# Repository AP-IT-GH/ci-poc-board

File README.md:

# Connected Island Proof of Concept Board

This board is used to gather data from many different sensors and send it over a LoRa network. 
The MCU on the board is an AT SAM D21 chosen because of it's low power capabilities and the extensive I/O options.
On board we have:
- 3 USART connection headers
- 1 I²C connection header
- 1 programming & debug connection
- RN2483 LoRaWAN module

The board can be powered with a voltage between 6.3V and 15V.

This document can be used to understand our reasoning behind certain choices and to learn how the board works. On the bottom we have a few improvements and suggestions for future versions.

The Bill of Materials to assemble the PCB can be found [here](./assets/bom/ibom.html) in HTML format.

## First Version

<figure>
<iframe src="https://myap84.autodesk360.com/shares/public/SH35dfcQT936092f0e434feaf45240fcc95f?mode=embed" width="1024" height="768" allowfullscreen="true" webkitallowfullscreen="true" mozallowfullscreen="true"  frameborder="0"></iframe>
<figcaption >Interactive 3D model of the PCB</figcaption>
</figure>

<figure>

<figcaption >Figure 1: Main Schematic</figcaption>
</figure>

<figure>

<figcaption >Figure 2: Power Regulators Schematic</figcaption>
</figure>

<figure>

<figcaption >Figure 3: RN2483 LoRaWAN module Schematic</figcaption>
</figure>

### Power Delivery

We are using a Li-Po 2 Cell battery and a LD1117 as 3.3V and 5V regulator

Li-Po 2 Cell: [Store](https://www.conrad.be/p/conrad-energy-lipo-accupack-74-v-2400-mah-aantal-cellen-2-20-c-softcase-xt60-1344133), [Datasheet](https://asset.conrad.com/media10/add/160267/c1/-/en/001344133SD01/veiligheidsvoorschriften-1344133-conrad-energy-lipo-accupack-74-v-2400-mah-aantal-cellen-2-20-c-softcase-xt60.pdf)

LD1117: [Store](https://www.conrad.be/p/stmicroelectronics-ld1117av33-spanningsregelaar-lineair-to-220ab-positief-vast-1-a-1184973), [Datasheet](https://asset.conrad.com/media10/add/160267/c1/-/en/001184973DS01/datablad-1184973-stmicroelectronics-ld1117av33-spanningsregelaar-lineair-to-220ab-positief-vast-1-a.pdf)

The LD1117 IC's are connected according to "Figure 3. Application circuit (for fixed output voltages)". 1x 5V en 1x 3.3V.

The dropout voltage of these regulators is 1.05V if we're counting for a 500mAh load. to get an output voltage of 5V, the regulator needs an input voltage of 5V + 1.05V = 6.05V. Thus our battery voltage has to stay above that value.

ADC voltage divider for battery:

R1 = 10 kOhm; R2 = 4.7 kOhm

### AT SAMD 21 Schematic Checklist

Datasheet p1108-p1118

#### Power Supply Connections

- [x] Check L1 10µH footprint. (https://be.farnell.com/tdk/vls201612hbx-100m-1/inductor-10uh-20-0-79a-shld/dp/2455369 ) (https://www.farnell.com/datasheets/2608157.pdf )

The MCU has two DVVIO pins (pin17 en pin36), these are internally connected to each other so only pin17 is in use.

#### External Analog Reference Connections

Not necessary because we are not using any external analog references.

#### External Reset Circuit

EFT = electrical fast transients -> spark when pressing a button

We don't need this EFT Immunity Enhancement so we're using "Figure 45-4. External Reset Circuit Schematic".

#### Clocks and Crystal Oscillators

[Understanding the SAM D21 clocks](https://blog.thea.codes/understanding-the-sam-d21-clocks/)

We keep the option to use an external 32,768kHz clock free, when not in use it doesn't have to be soldered on the PCB.

- [Capacitor](https://be.farnell.com/multicomp/mc0805n180j500ct/cap-18pf-50v-5-c0g-np0-0805/dp/1759194): MC0805N180J500CT, 18 pF, 0805
- [Crystal](https://be.farnell.com/fox-electronics/fx135a-327/crystal-32-768khz-12-5pf-smd/dp/2064037): FX135A-327, 32.768 kHz, SMD

Connected according to: "Figure 45-9. External Real Time Oscillator with Load Capacitor".

`XIN32` and `XOUT32` are on the only available connections for SERCOM1 (PA00 en PA01) so SERCOM1 will not be used.

#### Programming and Debug Ports

Pull-up resistor on SWCLK!

We are using "Figure 45-12. 10-pin JTAGICE3 Compatible Serial Wire Debug Interface".

#### USB Interface

We are not using the USB interface.

### SERCOM Aansluiten

The used SERCOM pins of the SAM D21 got a `SERCOMx_PADn_y` label for easy reference on the scheme and PCB. The Atmel START configuration was used as a reference.

SERCOM-ALT [ref1](https://microchipsupport.force.com/s/article/SERCOM-muxing-on-SAM-D-L-C-devices), [ref2](https://learn.adafruit.com/using-atsamd21-sercom-to-add-more-spi-i2c-serial-ports/muxing-it-up)

| Use case | SERCOM  | Pins           | Function                                                     |
| ------- | ------- | ---------------- | ----------------------------------------------------------- |
| RN2384  | SERCOM0 | PA04, PA05, PA07 | TX, RX, <span style="text-decoration:overline">RESET</span> |
| USART_1 | SERCOM5 | PA22, PA23       | TX, RX                                                      |
| USART_2 | SERCOM2 | PA08, PA09       | TX, RX                                                      |
| USART_3 | SERCOM3 | PA16, PA17       | TX, RX                                                      |
| I2C_0   | SERCOM4 | PA12, PA13       | SDA, SCL                                                    |

> If the PA24 and PA25 pins are not connected, it is recommended to enable a pull-up on PA24 and PA25 through input GPIO mode. The aim is to avoid an eventually extract power consumption (<1mA) due to a not stable level on pad. The port PA24 and PA25 doesn't have Drive Strength option. (these are the USB pins). 

[ATSAMD D21 Datasheet](https://ww1.microchip.com/downloads/en/DeviceDoc/SAM-D21DA1-Family-Data-Sheet-DS40001882G.pdf)

### RN2483 LoRaWAN module

[RN2483 Datasheet](https://ww1.microchip.com/downloads/en/DeviceDoc/RN2483-Low-Power-Long-Range-LoRa-Technology-Transceiver-Module-DS50002346F.pdf) 

Reuse of symbol from the older AirQualitySensor project.

`PA6` who is connected to `RN2384_RESET` should always be HIGH. You can reset the RN2483 module by setting the pin LOW for a moment.

<u>Are we using `UART_CTS` and `UART_RTS` as a handshake mechanism?</u>: No

<u>Do we connect the Internal Program Pins with the 6-pin ICSP header on our PCB?</u>: No

We are using RFH for 868MHz communication.

> When routing RF paths, use proper strip lines with an impedance of 50 Ohm.

We are not using the GPIO pins of the module.

## Future Versions

Luckily, the first version of this board works. Of course we have a few remarks to make for future versions of this board. 
A short summary:
- More marks on the silkscreen explaining the pinout of headers
- A different battery connector
- Adding a USB port
- Placing components on the back

### Markings

The first version of the board doesn't show any markings for the pinout of the headers. The battery connector doesn't even have a polarity marking. 

### Battery Connector

The current battery connector is very small and not very useful. A specific new connector has not been chosen yet.

### USB Port

We think that a USB port on the PCB would be very useful. There exists a bootloader for the ATSAMD 21 that enables users to program the board with CircuitPython. This might make the board easier to use. Other bootloaders enable the use of the Arduino IDE instead of Microchip Studio. 
Right now the board can only be programmed with a J-LINK or Atmel ICE programmer. 

### Components on the Back

Right now every component on the board is positioned on the front. We think a lot of space can be saved by placing some SMD components on the back.

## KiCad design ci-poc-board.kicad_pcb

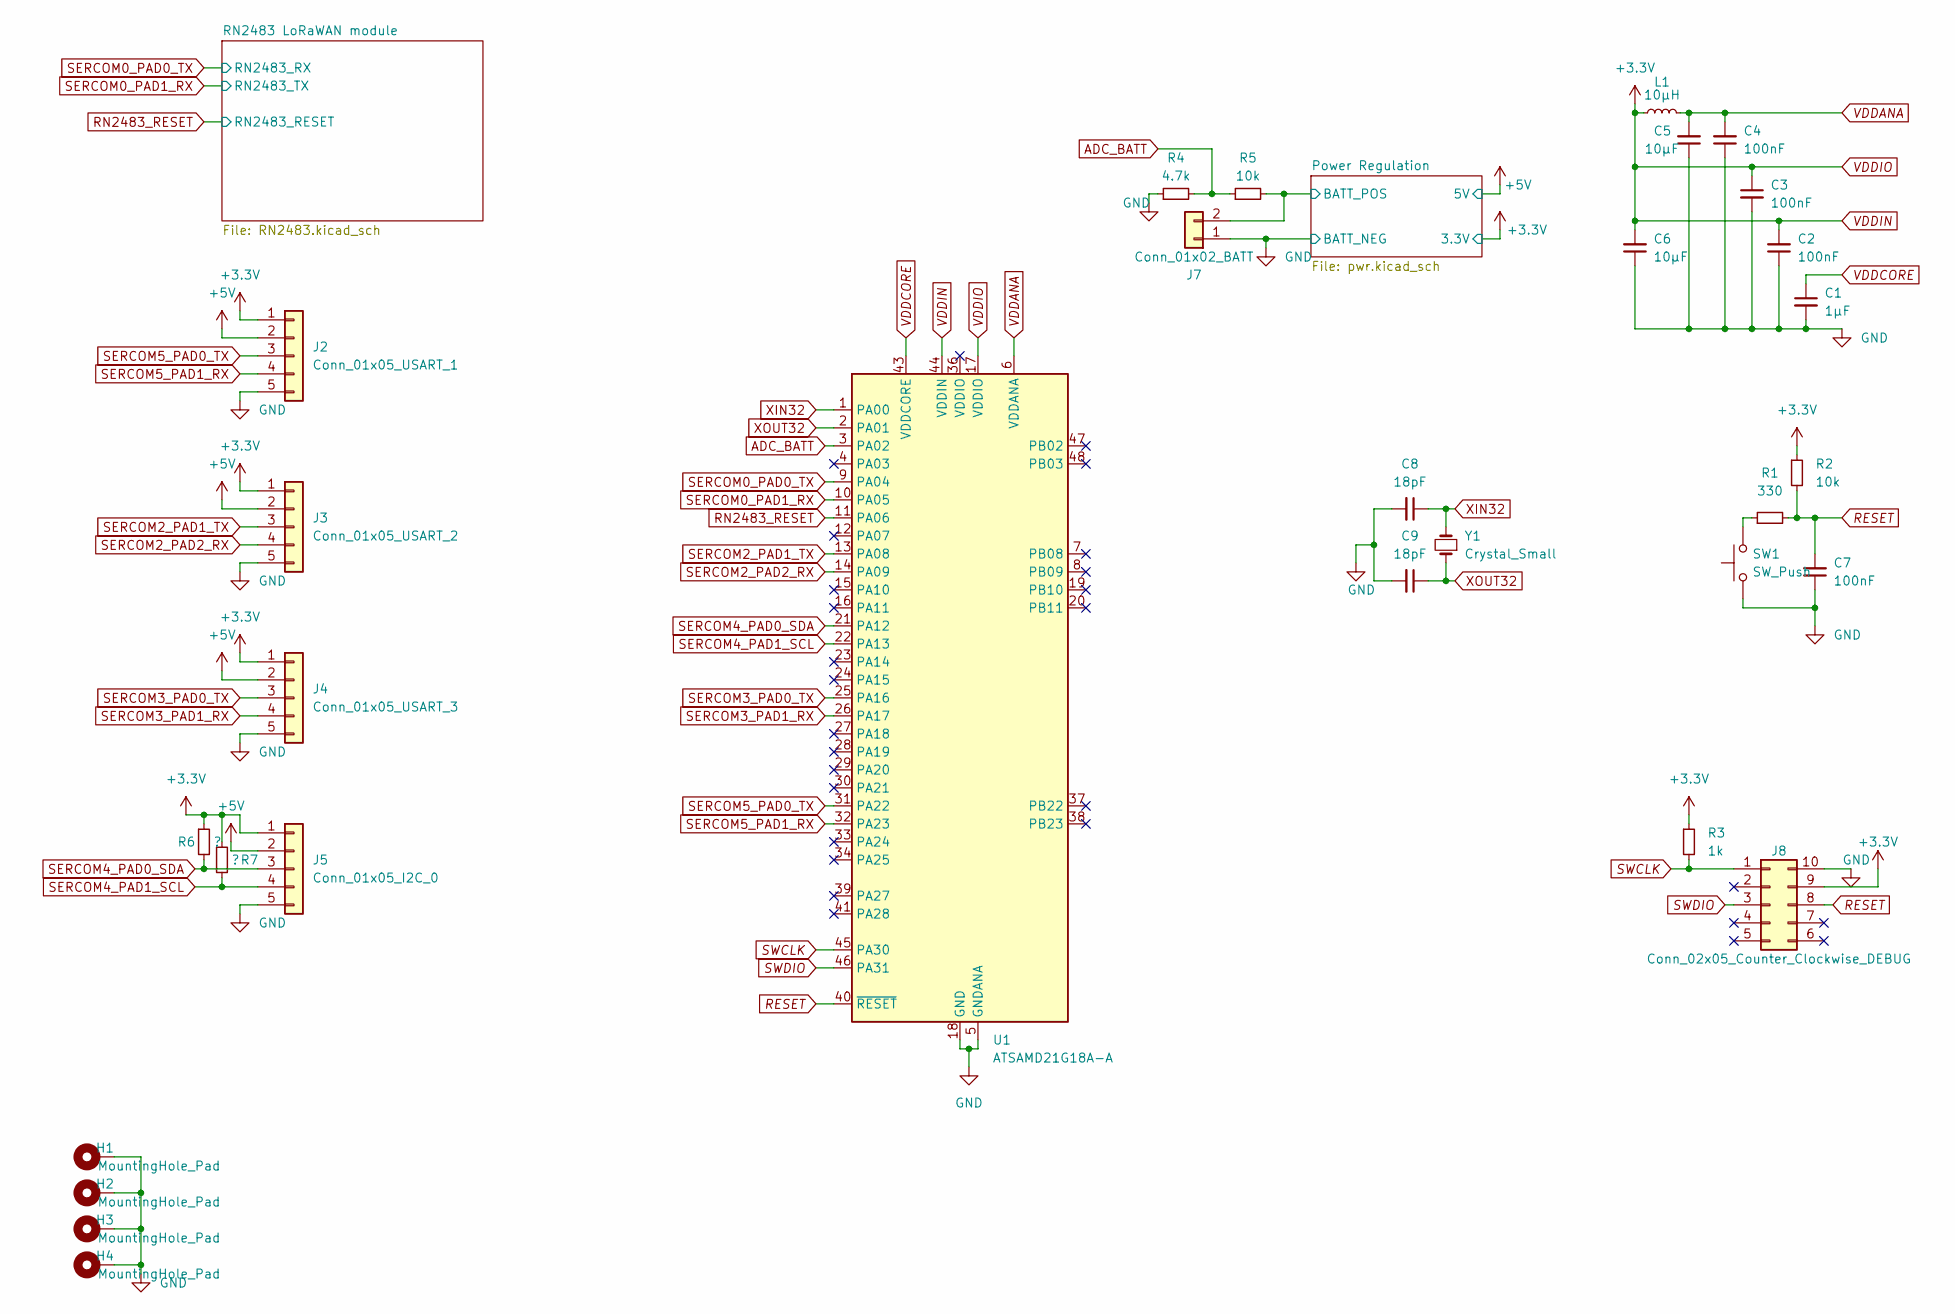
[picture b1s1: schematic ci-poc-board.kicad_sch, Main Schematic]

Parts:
C1: 1µF; C_0805_2012Metric_Pad1.18x1.45mm_HandSolder
C2, C3, C4, C7: 100nF; C_0805_2012Metric_Pad1.18x1.45mm_HandSolder
C5, C6: 10µF; C_0805_2012Metric_Pad1.18x1.45mm_HandSolder
C8, C9: 18pF; C_0805_2012Metric_Pad1.18x1.45mm_HandSolder
H1, H2, H3, H4: MountingHole_Pad; MountingHole_3.2mm_M3_DIN965_Pad
J2: Conn_01x05_USART_1; JST_XH_B5B-XH-A_1x05_P2.50mm_Vertical
J3: Conn_01x05_USART_2; JST_XH_B5B-XH-A_1x05_P2.50mm_Vertical
J4: Conn_01x05_USART_3; JST_XH_B5B-XH-A_1x05_P2.50mm_Vertical
J5: Conn_01x05_I2C_0; JST_XH_B5B-XH-A_1x05_P2.50mm_Vertical
J7: Conn_01x02_BATT; JST_PH_B2B-PH-K_1x02_P2.00mm_Vertical
J8: Conn_02x05_Counter_Clockwise_DEBUG; PinHeader_2x05_P2.54mm_Vertical
L1: 10µH; L_Murata_LQH2MCNxxxx02_2.0x1.6mm
R1: 330; R_0805_2012Metric_Pad1.20x1.40mm_HandSolder
R2, R5: 10k; R_0805_2012Metric_Pad1.20x1.40mm_HandSolder
R3: 1k; R_0805_2012Metric_Pad1.20x1.40mm_HandSolder
R4: 4.7k; R_0805_2012Metric_Pad1.20x1.40mm_HandSolder
R6, R7: ?; R_0805_2012Metric_Pad1.20x1.40mm_HandSolder
SW1: SW_Push; SW_Push_1P1T_NO_6x6mm_H9.5mm
U1: ATSAMD21G18A-A; TQFP-48_7x7mm_P0.5mm
Y1: Crystal_Small; Crystal_SMD_3215-2Pin_3.2x1.5mm

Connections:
+5V: J2.2, J3.2, J4.2, J5.2; also elsewhere on the board
/Power Regulation/BATT_POS: J7.2, R5.2; also elsewhere on the board
ADC_BATT: R4.2, R5.1, U1.3 (PA02)
GND: C1.2, C2.1, C3.2, C4.1, C5.1, C6.1, C7.1, C8.2, C9.2, H1.1, H2.1, H3.1, H4.1, J2.5, J3.5, J4.5, J5.5, J7.1, J8.10, R4.1, SW1.2, U1.5 (GNDANA), U1.18 (GND), U1.35 (GND), U1.42 (GND); also elsewhere on the board
unnamed: R1.1, SW1.1
RESET: C7.2, J8.8, R1.2, R2.2, U1.40 (~RESET)
RN2483_RESET: U1.11 (PA06); also elsewhere on the board
SERCOM0_PAD0_TX: U1.9 (PA04); also elsewhere on the board
SERCOM0_PAD1_RX: U1.10 (PA05); also elsewhere on the board
SERCOM2_PAD1_TX: J3.3, U1.13 (PA08)
SERCOM2_PAD2_RX: J3.4, U1.14 (PA09)
SERCOM3_PAD0_TX: J4.3, U1.25 (PA16)
SERCOM3_PAD1_RX: J4.4, U1.26 (PA17)
SERCOM4_PAD0_SDA: J5.3, R6.2, U1.21 (PA12)
SERCOM4_PAD1_SCL: J5.4, R7.2, U1.22 (PA13)
SERCOM5_PAD0_TX: J2.3, U1.31 (PA22)
SERCOM5_PAD1_RX: J2.4, U1.32 (PA23)
SWCLK: J8.1, R3.2, U1.45 (PA30)
SWDIO: J8.3, U1.46 (PA31)
VDDANA: C4.2, C5.2, L1.2, U1.6 (VDDANA)
VDDCORE: C1.1, U1.43 (VDDCORE)
VDDIN: C2.2, C3.1, C6.2, J2.1, J3.1, J4.1, J5.1, J8.9, L1.1, R2.1, R3.1, R6.1, R7.1, U1.17 (VDDIO), U1.44 (VDDIN); also elsewhere on the board
XIN32: C8.1, U1.1 (PA00), Y1.2
XOUT32: C9.1, U1.2 (PA01), Y1.1

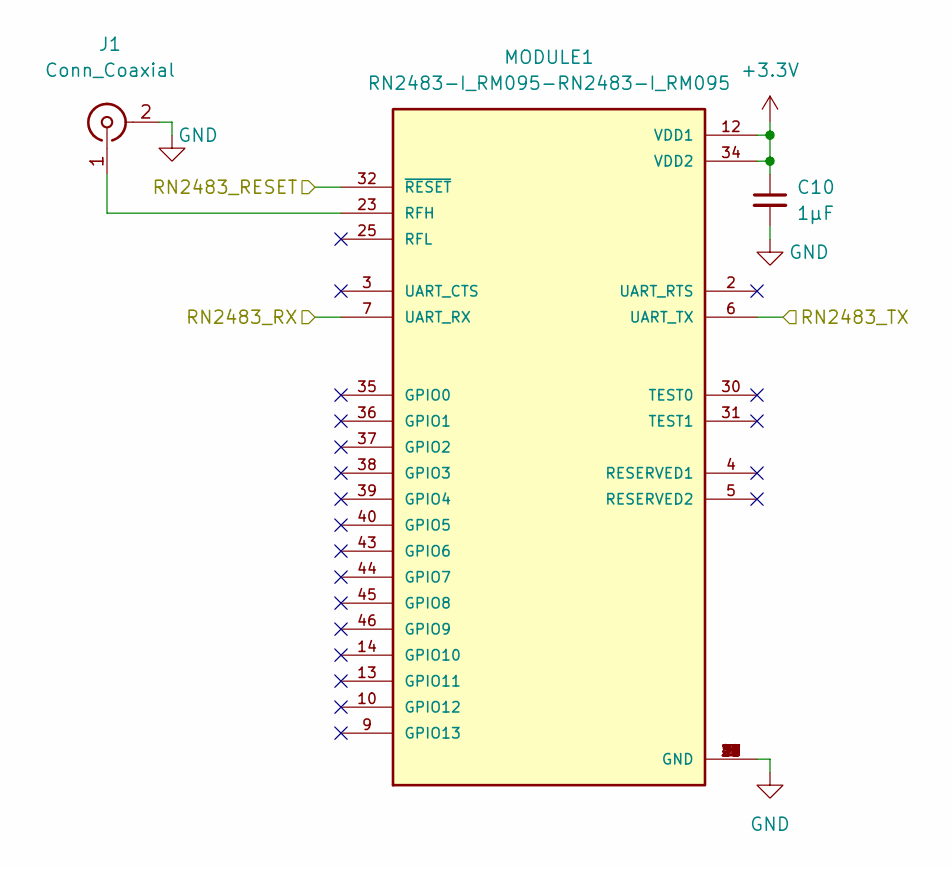
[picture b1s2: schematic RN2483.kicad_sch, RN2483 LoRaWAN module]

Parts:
C10: 1µF; C_0805_2012Metric_Pad1.18x1.45mm_HandSolder
J1: Conn_Coaxial; SMA_Amphenol_132289_EdgeMount
MODULE1: RN2483-I_RM095-RN2483-I_RM095; RN2483

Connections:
GND: C10.2, J1.2 (Ext), MODULE1.1 (GND), MODULE1.8 (GND), MODULE1.11 (GND), MODULE1.20 (GND), MODULE1.21 (GND), MODULE1.22 (GND), MODULE1.24 (GND), MODULE1.26 (GND), MODULE1.27 (GND), MODULE1.28 (GND), MODULE1.33 (GND), MODULE1.41 (GND), MODULE1.47 (GND); also elsewhere on the board
unnamed: J1.1 (In), MODULE1.23 (RFH)
RN2483_RESET: MODULE1.32 (~RESET); also elsewhere on the board
SERCOM0_PAD0_TX: MODULE1.7 (UART_RX); also elsewhere on the board
SERCOM0_PAD1_RX: MODULE1.6 (UART_TX); also elsewhere on the board
VDDIN: C10.1, MODULE1.12 (VDD1), MODULE1.34 (VDD2); also elsewhere on the board

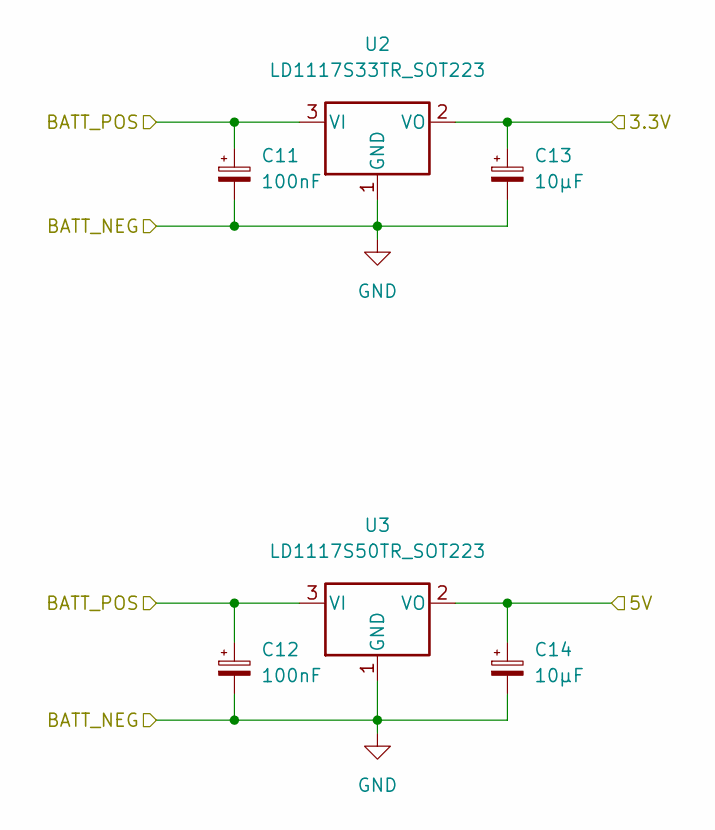
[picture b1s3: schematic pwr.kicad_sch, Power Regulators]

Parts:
C11, C12: 100nF; C_0805_2012Metric_Pad1.18x1.45mm_HandSolder
C13, C14: 10µF; C_0805_2012Metric_Pad1.18x1.45mm_HandSolder
U2: LD1117S33TR_SOT223; SOT-223-3_TabPin2
U3: LD1117S50TR_SOT223; SOT-223-3_TabPin2

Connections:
+5V: C14.1, U3.2 (VO); also elsewhere on the board
/Power Regulation/BATT_POS: C11.1, C12.1, U2.3 (VI), U3.3 (VI); also elsewhere on the board
GND: C11.2, C12.2, C13.2, C14.2, U2.1 (GND), U3.1 (GND); also elsewhere on the board
VDDIN: C13.1, U2.2 (VO); also elsewhere on the board

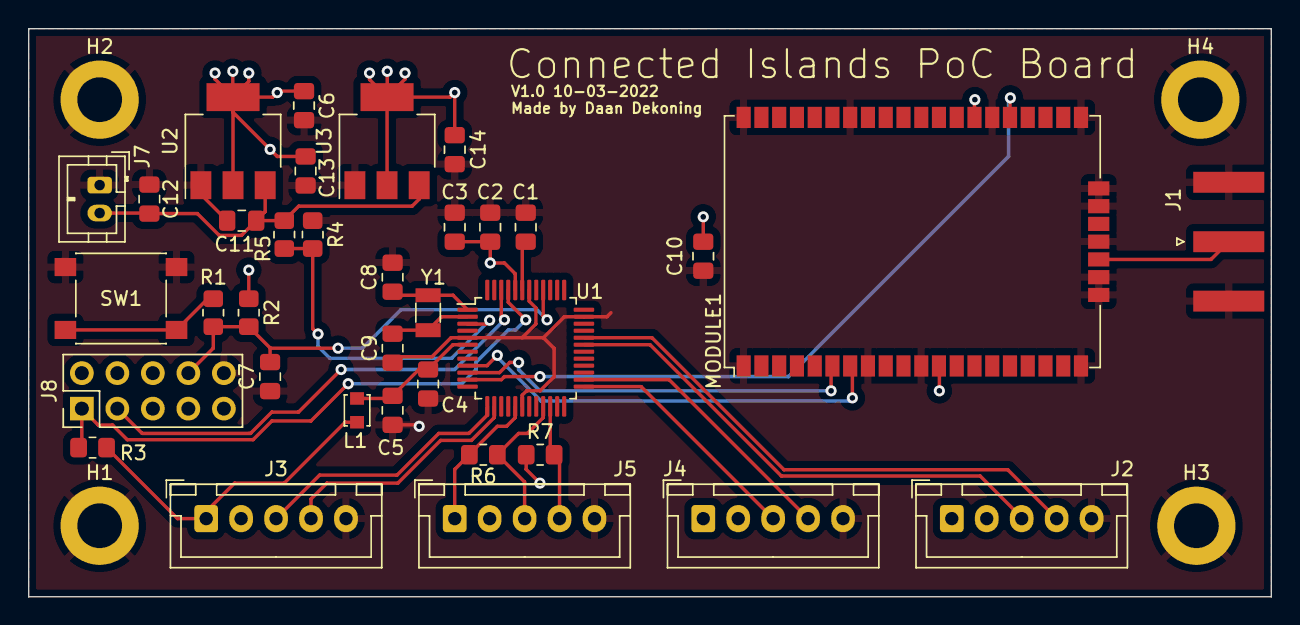
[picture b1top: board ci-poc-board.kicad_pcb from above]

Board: 4 copper layers, 88.9 x 40.6 mm, 39 parts (0 on the bottom side), 25 nets.

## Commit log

2022-02-14 initial commit v1
2022-02-14 USART, SPI en I2C connecties gemaakt. OSC toegevoegd. JTAG ICE compatible interface toegevoegd.
2022-02-16 Added Atmel START config file
2022-02-16 Added RN2483 LoRa Module, battery connection, oscillator, 3.3V and 5V regulator. Removed SPI
2022-02-28 Finishing schematic, first iteration of PCB
2022-03-04 Moved SMA connector to the edge
2022-03-09 Small changes. Added BOM
2022-03-10 Added title and date to PCB, added render to README.md
2022-04-20 Translated documentation from Dutch to English
2022-04-24 Added future plans
2022-05-11 Edited documentation
2022-05-11 Make KiCad project more portable
